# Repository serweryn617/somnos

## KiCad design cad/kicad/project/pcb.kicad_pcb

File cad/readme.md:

# Somnos CAD Files

---

Initial PCB prototype notes:
 - resistors missing on USB-C CC pins!
 - update INA219 footprint so it better matches the module,
 - disconnect clkout pin - unused ethernet module output pin.

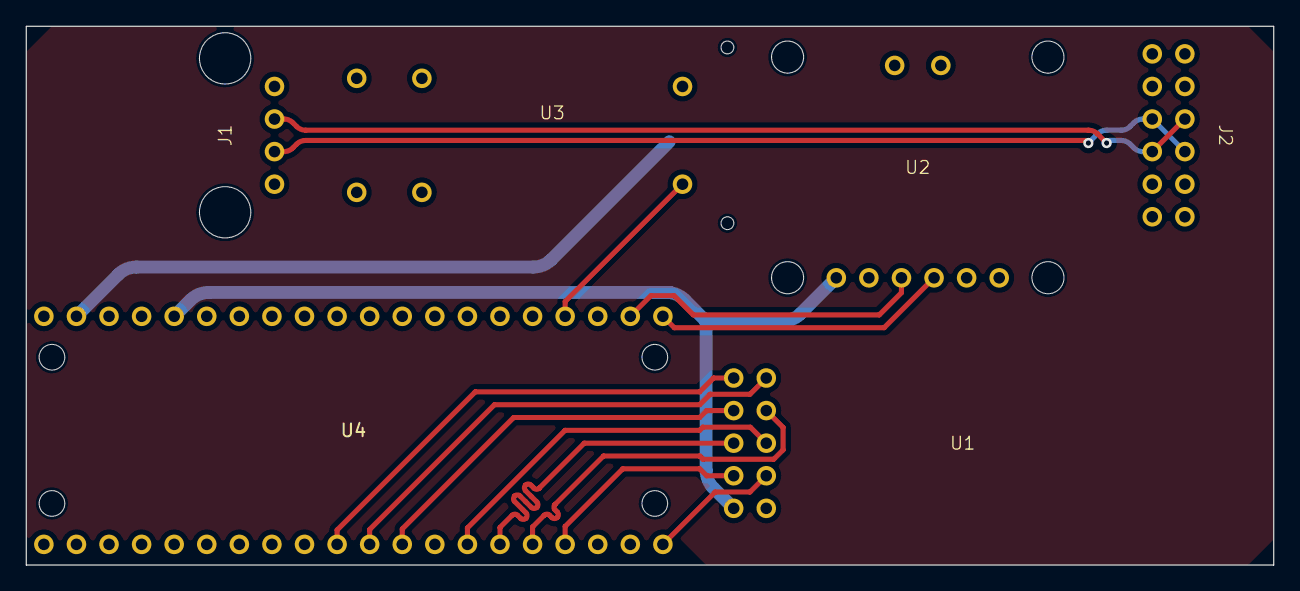
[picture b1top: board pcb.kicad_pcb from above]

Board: 2 copper layers, 97.2 x 42.0 mm, 6 parts (0 on the bottom side), 18 nets.

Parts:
J1: USB_A; USB A Port
J2: USB_C_Receptacle_USB2.0; USB C Port
U1: END28J60
U2: INA219
U3: N-MOS_1
U4: PiPico

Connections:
/USB_D+: J1.3 (D+), J2.A6 (D+), J2.B6 (D+)
/USB_D-: J1.2 (D-), J2.A7 (D-), J2.B7 (D-)
unnamed: J1.4 (GND), U3.O- (VOUT-)
unnamed: J1.1 (VBUS), U2.1 (VIN-), U4.39 (VSYS)
unnamed: U1.10 (CLK), U4.10 (GP7)
unnamed: U1.4 (CS), U4.17 (GP13)
unnamed: J2.A1 (GND), U1.1 (GND), U2.4 (GND), U3.G (GND), U3.I- (VIN-), U4.3 (GND), U4.8 (GND), U4.13 (GND), U4.18 (GND), U4.23 (GND), U4.28 (GND), U4.33 (GND), U4.38 (GND)
unnamed: U1.9 (INT), U4.11 (GP8)
unnamed: U1.3 (RST), U4.20 (GP15)
unnamed: U1.5 (SCK), U4.14 (GP10)
unnamed: U1.6 (SI), U4.15 (GP11)
unnamed: U1.7 (SO), U4.16 (GP12)
unnamed: U1.2 (VCC), U2.3 (VCC), U4.36 (3V3(OUT))
unnamed: U1.8 (WOL), U4.12 (GP9)
unnamed: U2.5 (SCL), U4.22 (GP17)
unnamed: U2.6 (SDA), U4.21 (GP16)
unnamed: J2.A4 (VBUS), U2.2 (VIN+)
unnamed: U3.T (TRIG), U4.24 (GP18)

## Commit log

2023-11-01 Initial commit (INA219, D-RAL, build system)
2023-11-01 Fix build
2023-11-01 I2C cleanup
2023-11-01 Add register fields to ENC28J60 common regs
2023-11-01 Add register fields to ENC28J60 Ethernet regs
2023-11-01 Add register fields to ENC28J60 MAC regs
2023-11-01 Add register fields to ENC28J60 MII regs
2023-11-01 Update ENC28J60 D-RAL
2023-11-01 Update dockerfile
2023-11-01 initial enc template
2023-11-01 Sort out enc template
2023-11-01 WIP UDP send
2023-11-01 Add tinyusb back to Dockerfile
2023-11-03 Update pin and interface numbers
2023-11-03 Ignore CAD files
2023-11-03 Add clang-format initial
2023-11-03 Clang v2
2023-11-04 Add pico-sdk as submodule
2023-11-04 Add picotool submodule
2023-11-04 Update build system
2023-11-04 Add pico-sdk as submodule (#1)
    * Add pico-sdk submodule
    * Add picotool submodule
    * Update build system
2023-11-04 Move enc28j60 to D-RAL
2023-11-04 Fix SPI CS
2023-11-04 Some fixes
2023-11-04 Remove this
2023-11-04 Fix MAC address order
2023-11-04 Add D-RAL submodule
2023-11-04 Update ENC D-RAL
2023-11-04 Add PHY regs
2023-11-04 INA219 rewrite
2023-11-05 ENC28J60 and SPI driver rewrite
2023-11-05 Register model update to variable reg size
2023-11-05 Fix SPI driver init
2023-11-05 Fix init order
2023-11-05 Remove d-ral from gitignore
2023-11-05 Massive development branch merge (#2)
    * initial enc28j60 template
    * Sort out enc28j60 template
    * Send UDP packets
    * Update pin and interface numbers
    * Add clang-format initial
    * Add pico-sdk submodule
2023-11-05 Send out measurement data; add host app
2023-11-05 Update D-RAL model
2023-11-10 enc wip
2023-11-10 Finished enc rewrite and namespace madness
2023-11-10 Enums
2023-11-10 Add namespace in main
2023-11-10 ENC28J60 rewrite (#3)
    * Fix SPI CS
    * enc rewrite and namespace madness
    * Enums rework
2023-11-10 Added namespaces
2023-11-10 Firmware directory restructure
2023-11-10 Move submodules
2023-11-10 Update project script
2023-11-10 Autoformat
2023-11-10 Create driver definitions
2023-11-11 Recovered CAD files
2023-11-11 Add pico step
2023-11-11 Add readme
2023-11-11 Extend KiCAD todo list
2023-11-11 Update readme build command
2023-11-11 Add hardware defs
2023-11-11 Network interface rewrite in progress
2023-11-11 Fix SPI port number
2023-11-11 Fix mistakes
2023-11-11 Change some names
2023-11-12 lwIP working in OOP paradigm
2023-11-12 Name change
2023-11-13 Quick format; added lwip reference link
2023-11-18 Further network interface cleanup
2023-11-18 UDP receive investigated
2023-11-19 Fix UDP bidirectional traffic
2023-11-19 Network interface initial rework (#4)
    * Network interface rewrite in progress
    * Fix SPI port number
    * Fix mistakes
    * Change some names
    * Autoformat
    * lwIP working in OOP paradigm
2023-11-19 General project restructure
2023-11-19 Changed imports to fit new project structure
2023-11-19 Project Restructure (#5)
    * General project restructure
    * Changed imports to fit new project structure
2023-11-20 Enhance UDP receiver script
2023-11-20 Static code analysis
2023-11-25 Make data sending more flexible
2023-11-25 Update udp receiver
2023-12-09 Add D-RAL v0.5.0 submodule
2023-12-09 Update D-RAL adapter and templates
2023-12-30 Remove mainline D-RAL
2023-12-30 Use custom D-RAL fork
2023-12-30 Update code for new D-RAL
2023-12-30 Generate D-RALs with new version
2023-12-30 Update D-RAL to v0.5.0 (#7)
    * Add D-RAL v0.5.0 submodule
    * Update D-RAL adapter and templates
    * Remove mainline D-RAL
    * Use custom D-RAL fork
    * Update code for new D-RAL
    * Generate D-RALs with new version
2023-12-31 INA219 new configuration and fixes
2024-01-01 Remove picotool
2024-01-01 Use new payload structure
2024-01-01 Update UDP communication script
2024-01-01 Add capability to receive UDP data (#6)
    * Update UDP receiver
    * Update UDP communication script
2024-01-01 Send data to requested IP address
2024-01-01 Add Prometheus scripts and readme
2024-01-01 Picotool leftover
2024-01-01 Add better project description
2024-01-01 Update Prometheus scripts readme
2024-01-06 Remove f-string
2024-01-06 Send data to requested port
2024-01-06 Update Python scripts for new port behavior
2024-01-06 Slight description modification
2024-01-06 Move MOSFET pin to hw
2024-01-26 Added missing models
2024-01-27 Top housing general shape done
2024-01-27 Updated Freecad data
2024-01-27 Add CAD data
2024-01-30 Remove dral fork
2024-01-30 Use mainline D-RAL
2024-01-30 Peripheral base address workaround
2024-01-30 Re-generate D-RAL
2024-01-30 Update to mainline D-RAL v0.5.1 (#9)
    * Remove dral fork
    * Use mainline D-RAL
    * Peripheral base address workaround
    * Re-generate D-RAL
